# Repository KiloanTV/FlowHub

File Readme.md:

<div>
  <h1 align="center">FlowHub V1</h1>

  <p align="center">
  <a href="https://blueprint.hackclub.com/">
    </img>
  </a>
  </p>
  <h1></h1>
  <p align="center">
    ESP8266-based PC fan controller for Racks.
  </p>
</div>

<sub align="center">This work is licensed under the
[MIT License](https://mit-license.org).
</sub>

## Table of Contents

- [About](#about)
- [Pictures](#pictures)
- [Bill of Materials](#bill-of-materials)

# About

So I had the idea to develop a central control unit for PC fans, more precisely, one for a mobile rack that also houses computers. Then I could control the fan speeds independently of the individual computers. As I said, I needed this for my rack, which I used for learning and experimenting, so I built a simple PCB with a case for this purpose.

# Pictures

# Bill of Materials

<details>
<summary><strong>Show Bill Of Materials(BOM) ----></strong></summary>

|Designator|Footprint                                  |Quantity|Value               |LCSC Part #|
|----------|-------------------------------------------|--------|--------------------|-----------|
|C1        |0805                                       |1       |10uF                |C2897295   |
|C2        |CP_Radial_D10.0mm_P5.00mm                  |1       |1000uF              |C10750     |
|D1        |D_SMA_Handsoldering                        |1       |Diode               |C22452     |
|J1        |TerminalBlock_4Ucon_1x02_P3.50mm_Horizontal|1       |Power IN            |C695629    |
|J2        |PinHeader_1x04_P2.54mm_Vertical            |1       |Prog                |C52016392  |
|J3        |PinHeader_1x04_P2.54mm_pclüfter            |1       |Lüfter1             |C722747    |
|J4        |PinHeader_1x04_P2.54mm_pclüfter            |1       |Lüfter2             |C722747    |
|J5        |PinHeader_1x04_P2.54mm_pclüfter            |1       |Lüfter3             |C722747    |
|J6        |PinHeader_1x04_P2.54mm_pclüfter            |1       |Lüfter4             |C722747    |
|J7        |PinHeader_1x04_P2.54mm_pclüfter            |1       |Lüfter5             |C722747    |
|Q1        |TO-263-2                                   |1       |IRF9Z34NSTRLPBF-JSM |C21714355  |
|Q2        |TO-92                                      |1       |Transistor 45V 100mA|C900800    |
|R1        |0805                                       |1       |2.2kΩ               |C17520     |
|R2        |0805                                       |1       |10kΩ                |C84376     |
|R3, R4    |0805                                       |2       |1kΩ                 |C95781     |
|SW1       |SW_SPST_SKQG_WithStem                      |1       |Reset               |C116647    |
|SW2       |SW_SPST_SKQG_WithStem                      |1       |Boot                |C116647    |
|U1        |SOT223-3_ONS                               |1       |NCP1117LPST33T3G    |C146799    |
|U2        |ESP-12E                                    |1       |ESP-12F             |C82891     |
|Quote from LCSC: $21.43 Quote from JLCPCB: $28,68       |                                           |        |                    |           |

</details>

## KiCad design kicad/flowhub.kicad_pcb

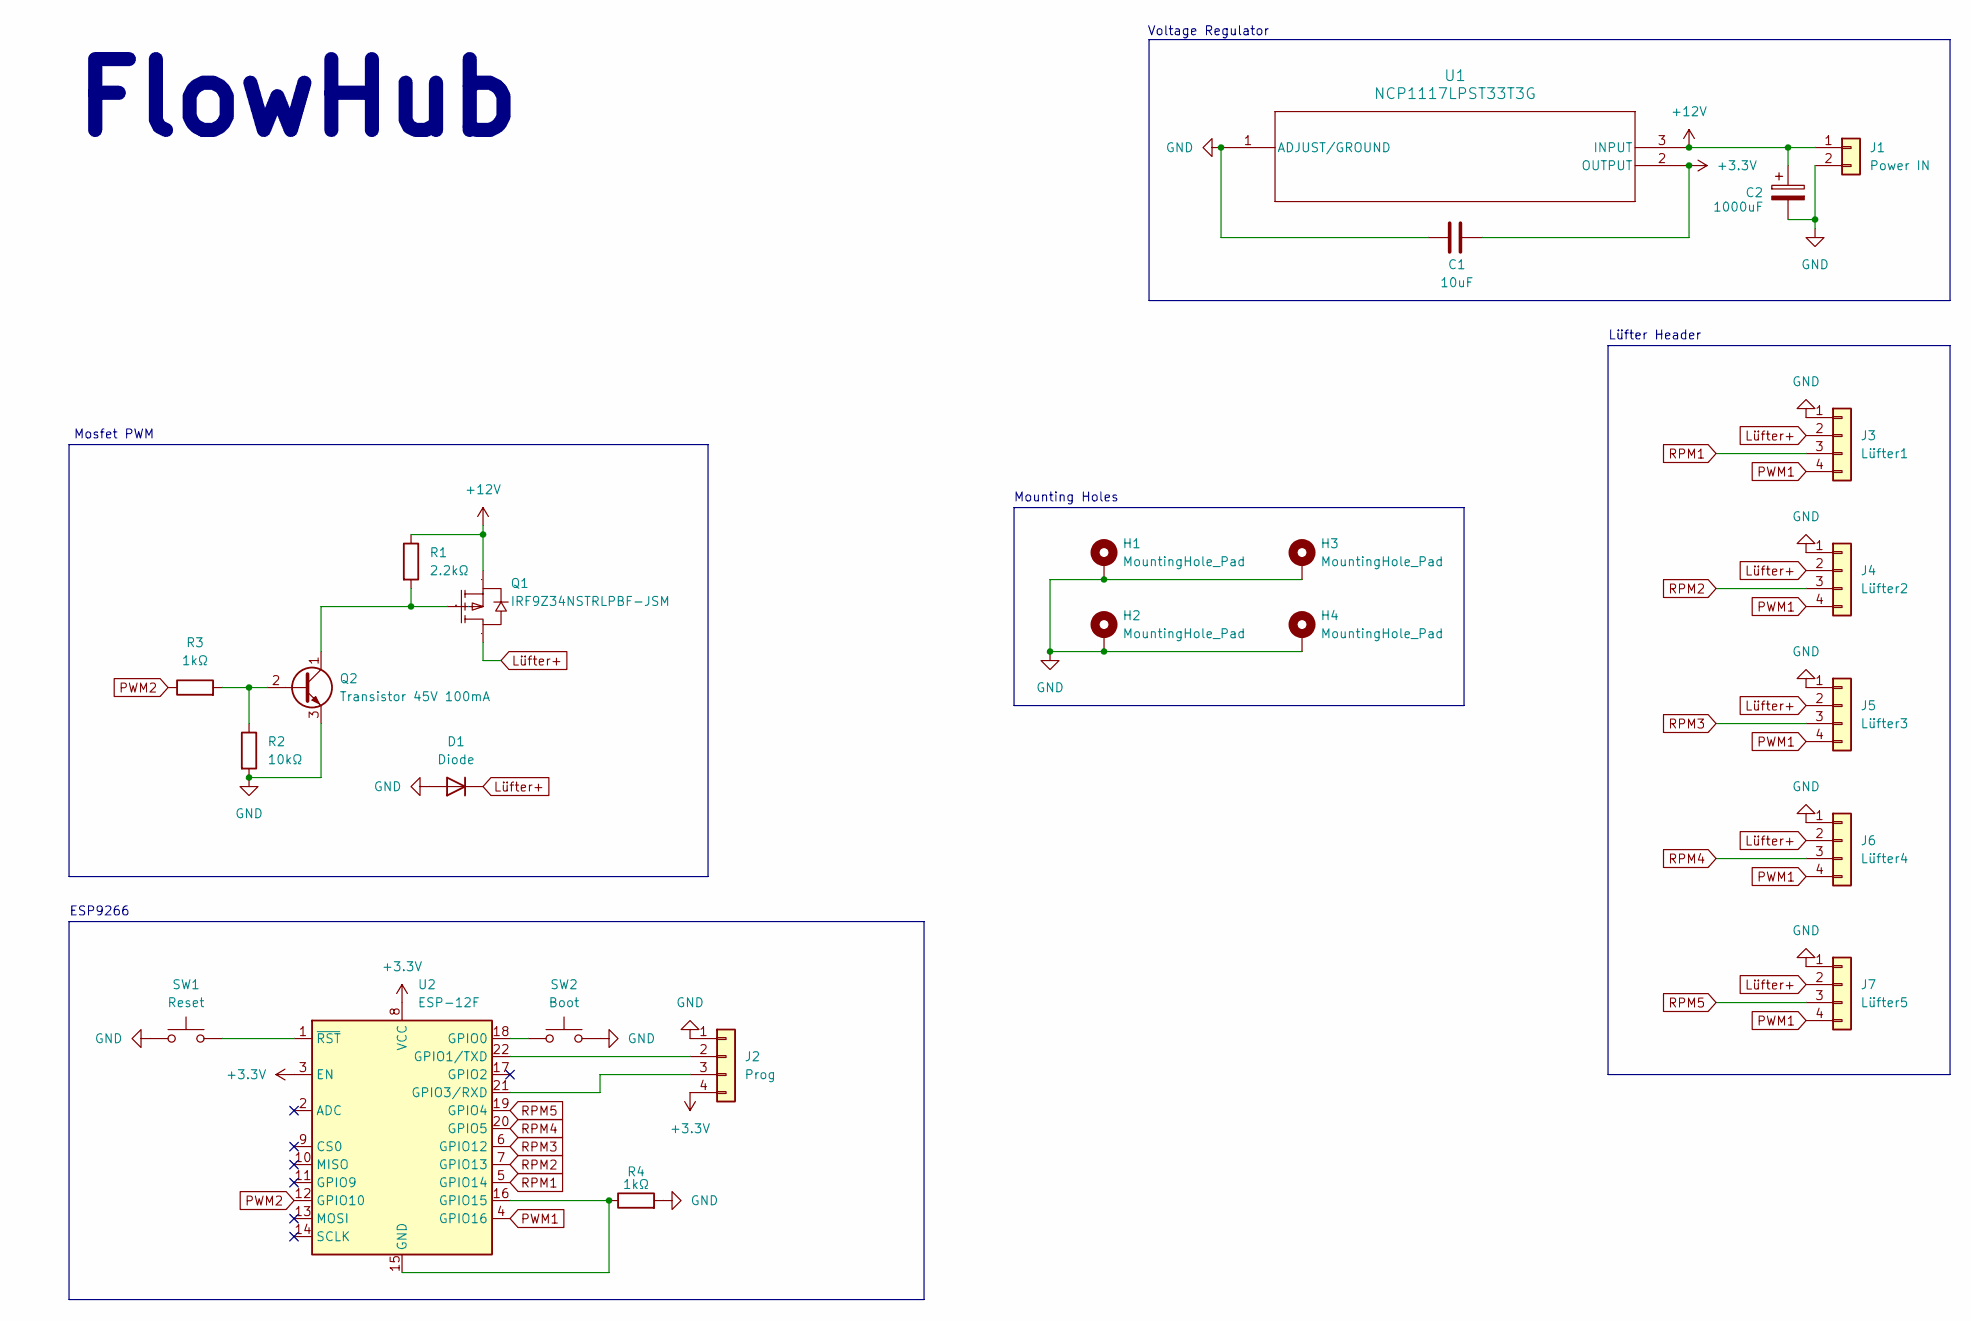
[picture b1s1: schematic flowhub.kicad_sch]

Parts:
C1: 10uF; C_0805_2012Metric_Pad1.18x1.45mm_HandSolder; LCSC C2897295
C2: 1000uF; CP_Radial_D10.0mm_P5.00mm; LCSC C10750
D1: Diode; D_SMA_Handsoldering; LCSC C22452
H1, H2, H3, H4: MountingHole_Pad; MountingHole_2.2mm_M2_Pad_Via
J1: Power IN; TerminalBlock_4Ucon_1x02_P3.50mm_Horizontal; LCSC C695629
J2: Prog; PinHeader_1x04_P2.54mm_Vertical; LCSC C52016392
J3: Lüfter1; PinHeader_1x04_P2.54mm_pclüfter; LCSC C722747
J4: Lüfter2; PinHeader_1x04_P2.54mm_pclüfter; LCSC C722747
J5: Lüfter3; PinHeader_1x04_P2.54mm_pclüfter; LCSC C722747
J6: Lüfter4; PinHeader_1x04_P2.54mm_pclüfter; LCSC C722747
J7: Lüfter5; PinHeader_1x04_P2.54mm_pclüfter; LCSC C722747
Q1: IRF9Z34NSTRLPBF-JSM; TO-263-2; LCSC C21714355
Q2: Transistor 45V 100mA; TO-92; LCSC C900800
R1: 2.2kΩ; R_0805_2012Metric_Pad1.20x1.40mm_HandSolder; LCSC C17520
R2: 10kΩ; R_0805_2012Metric_Pad1.20x1.40mm_HandSolder; LCSC C84376
R3, R4: 1kΩ; R_0805_2012Metric_Pad1.20x1.40mm_HandSolder; LCSC C95781
SW1: Reset; SW_SPST_SKQG_WithStem; LCSC C116647
SW2: Boot; SW_SPST_SKQG_WithStem; LCSC C116647
U1: NCP1117LPST33T3G; SOT223-3_ONS; LCSC C146799
U2: ESP-12F; ESP-12E; LCSC C82891

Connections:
+3.3V: C1.1, J2.4, U1.2 (OUTPUT), U2.3 (EN), U2.8 (VCC)
+12V: C2.1, J1.1, Q1.3, R1.1, U1.3 (INPUT)
GND: C1.2, C2.2, D1.2 (A), H1.1, H2.1, H3.1, H4.1, J1.2, J2.1, J3.1, J4.1, J5.1, J6.1, J7.1, Q2.3 (C), R2.2, R4.2, SW1.1, SW2.2, U1.1 (ADJUST/GROUND)
Lüfter+: D1.1 (K), J3.2, J4.2, J5.2, J6.2, J7.2, Q1.2
unnamed: J2.2, U2.22 (GPIO1/TXD)
unnamed: J2.3, U2.21 (GPIO3/RXD)
unnamed: Q2.2 (B), R2.1, R3.2
unnamed: Q1.1, Q2.1 (E), R1.2
unnamed: R4.1, U2.15 (GND), U2.16 (GPIO15)
unnamed: SW2.1, U2.18 (GPIO0)
unnamed: SW1.2, U2.1 (~RST)
PWM1: J3.4, J4.4, J5.4, J6.4, J7.4, U2.4 (GPIO16)
PWM2: R3.1, U2.12 (GPIO10)
RPM1: J3.3, U2.5 (GPIO14)
RPM2: J4.3, U2.7 (GPIO13)
RPM3: J5.3, U2.6 (GPIO12)
RPM4: J6.3, U2.20 (GPIO5)
RPM5: J7.3, U2.19 (GPIO4)

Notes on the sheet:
Mosfet PWM
Voltage Regulator
ESP9266
Lüfter Header
FlowHub
Mounting Holes

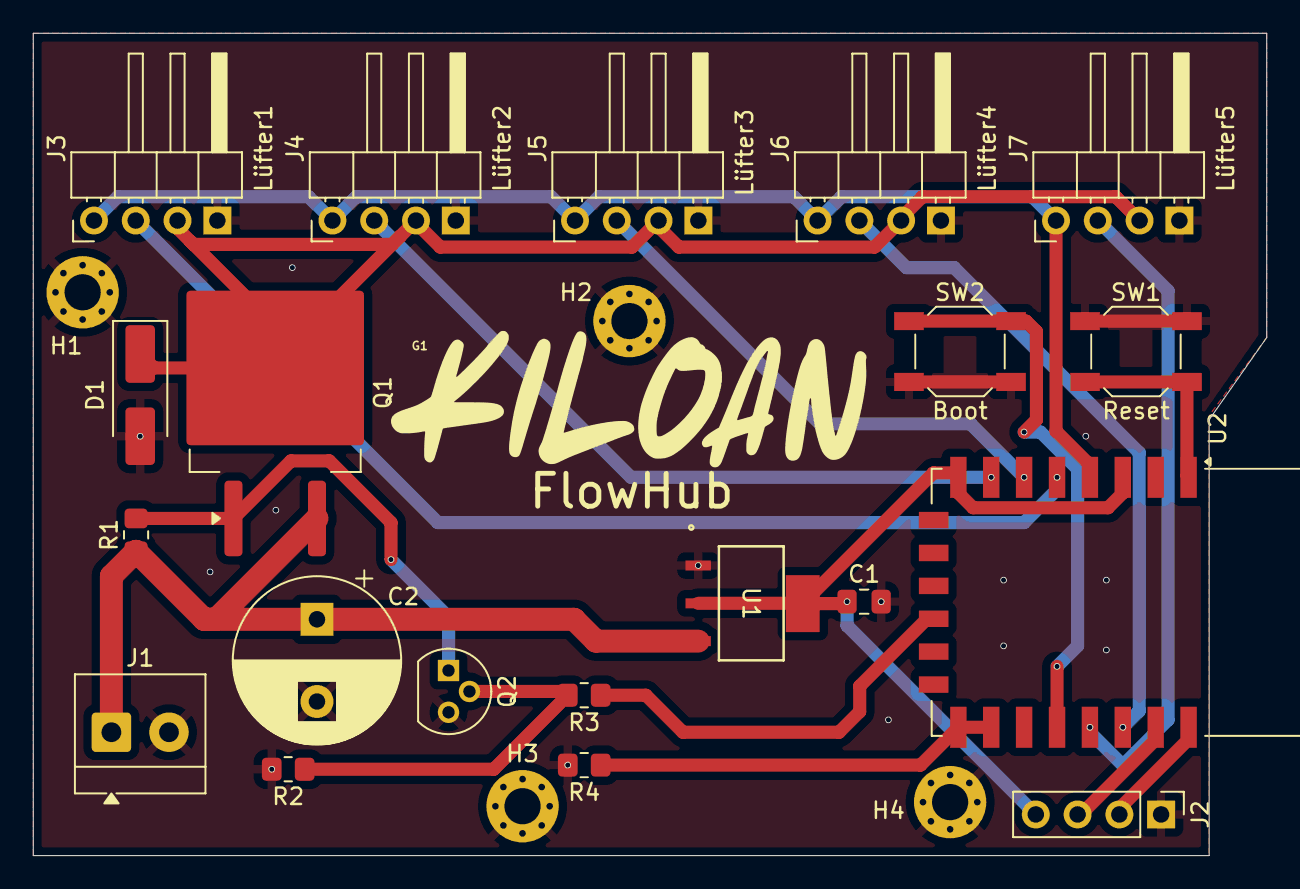
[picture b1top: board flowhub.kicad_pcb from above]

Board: 2 copper layers, 75.0 x 50.0 mm, 25 parts (0 on the bottom side), 18 nets.

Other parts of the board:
G1: LOGO

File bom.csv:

Designator,Footprint,Quantity,Value,LCSC Part #
C1,0805,1,10uF,C2897295
C2,CP_Radial_D10.0mm_P5.00mm,1,1000uF,C10750
D1,D_SMA_Handsoldering,1,Diode,C22452
J1,TerminalBlock_4Ucon_1x02_P3.50mm_Horizontal,1,Power IN,
J2,PinHeader_1x04_P2.54mm_Vertical,1,Prog,C52016392
J3,PinHeader_1x04_P2.54mm_pclüfter,1,Lüfter1,C722747
J4,PinHeader_1x04_P2.54mm_pclüfter,1,Lüfter2,C722747
J5,PinHeader_1x04_P2.54mm_pclüfter,1,Lüfter3,C722747
J6,PinHeader_1x04_P2.54mm_pclüfter,1,Lüfter4,C722747
J7,PinHeader_1x04_P2.54mm_pclüfter,1,Lüfter5,C722747
Q1,TO-263-2,1,IRF9Z34NSTRLPBF-JSM,C21714355
Q2,TO-92,1,Transistor 45V 100mA,
R1,0805,1,2.2kΩ,C17520
R2,0805,1,10kΩ,C84376
"R3, R4",0805,2,1kΩ,C95781
SW1,SW_SPST_SKQG_WithStem,1,Reset,C116647
SW2,SW_SPST_SKQG_WithStem,1,Boot,C116647
U1,SOT223-3_ONS,1,NCP1117LPST33T3G,C146799
U2,ESP-12E,1,ESP-12F,C82891

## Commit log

2025-11-22 Initial commit
    _ Kian
